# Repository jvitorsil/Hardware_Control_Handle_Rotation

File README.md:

# Hardware_Control_Handle_Rotation

Sistema embarcado para controle de rotação de punho em próteses bioelétricas através de sensores inerciais.

O sistema conta com a utilização de dois acelerometro acoplados ao paciente, acoplados respectivamente em paralelo na região antero-lateral do torax nos musculos intercostais e outro localizado no triceps braquial. O funcionamento está baseado na agulação criada entre os sensores pelo movimento de abdução do braço, gerando assim um movimento de pronação e supinação da protese.

O circuito eletronico conta com a utilização de um micrcontrolador STM32F103C8T6, com toda parte de Debug, reset e clock adicionada ao circuito. 

As proteses mioeletricas atuais contam na maioria das vezes com motores DC e para o acionamento do mesmo foi utilizado do driver L293D, que consegue controlar a velocidade e sentido de rotação do motor através da modulação dos pulsos de PWM gerado.

Já para a parte de entrada de dados foi definido o sensor MPU6050, contando com protocolo de comunicação I2C.

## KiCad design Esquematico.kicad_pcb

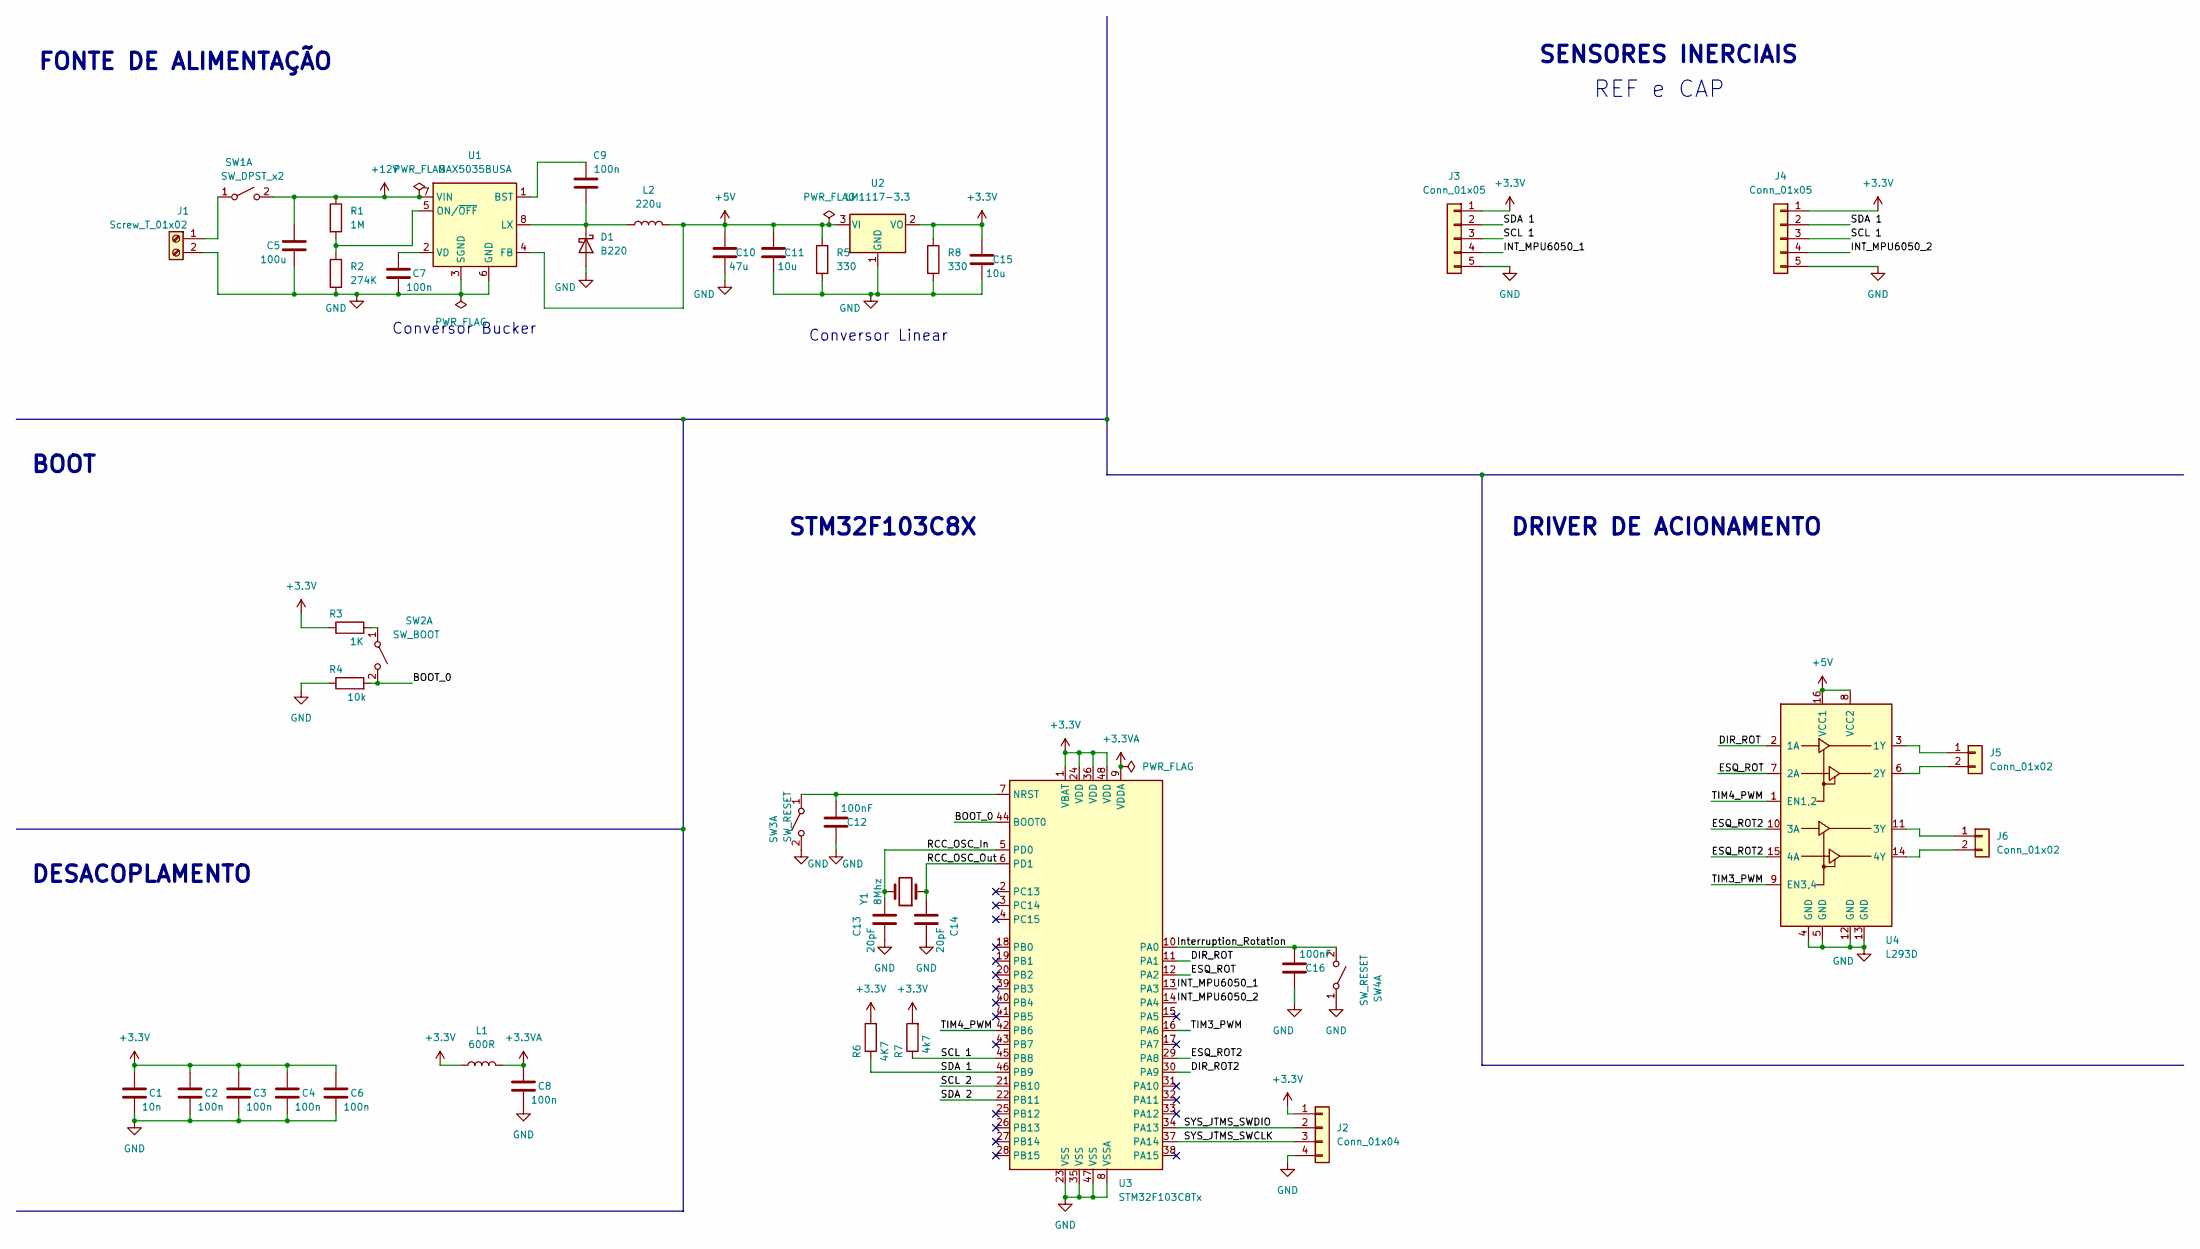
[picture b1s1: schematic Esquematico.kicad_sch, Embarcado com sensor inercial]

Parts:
C1: 10n; C_0402_1005Metric
C2, C3, C4, C6, C8: 100n; C_0402_1005Metric
C5: 100u; C_0805_2012Metric
C7, C9: 100n; C_0805_2012Metric
C10: 47u; C_0805_2012Metric
C11, C15: 10u; C_0805_2012Metric
C12, C16: 100nF; C_0402_1005Metric
C13, C14: 20pF; C_0603_1608Metric
D1: B220; D_SMF
J1: Screw_T_01x02; JST_PH_S2B-PH-SM4-TB_1x02-1MP_P2.00mm_Horizontal
J2: Conn_01x04; JST_PH_S4B-PH-SM4-TB_1x04-1MP_P2.00mm_Horizontal
J3, J4: Conn_01x05; JST_PH_S5B-PH-SM4-TB_1x05-1MP_P2.00mm_Horizontal
J5, J6: Conn_01x02; JST_PH_S2B-PH-SM4-TB_1x02-1MP_P2.00mm_Horizontal
L1: 600R; L_0603_1608Metric
L2: 220u; L_0603_1608Metric
R1: 1M; R_0805_2012Metric
R2: 274K; R_0805_2012Metric
R3: 1K; R_0805_2012Metric
R4: 10k; R_0805_2012Metric
R5, R8: 330; R_0805_2012Metric
R6: 4K7; R_0805_2012Metric
R7: 4k7; R_0805_2012Metric
SW1: SW_DPST_x2; SW_DIP_SPSTx01_Slide_6.7x4.1mm_W6.73mm_P2.54mm_LowProfile_J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
SW2: SW_BOOT; SW_SPST_B3U-1000P-B
SW3, SW4: SW_RESET; SW_SPST_B3U-1000P-B
U1: MAX5035BUSA; SOIC-8_3.9x4.9mm_P1.27mm
U2: LM1117-3.3; SOT-223-3_TabPin2
U3: STM32F103C8Tx; LQFP-48_7x7mm_P0.5mm
U4: L293D; DIP-16_W7.62mm
Y1: 8Mhz; Crystal_SMD_HC49-SD

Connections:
+3.3V: C1.1, C2.1, C3.1, C4.1, C6.1, C15.2, J2.1, J3.1, J4.1, L1.1, R3.1, R6.2, R7.2, R8.1, U2.2 (VO), U3.1 (VBAT), U3.24 (VDD), U3.36 (VDD), U3.48 (VDD)
+3.3VA: C8.1, L1.2, U3.9 (VDDA)
+5V: C10.2, C11.2, L2.2, R5.1, U1.4 (FB), U2.3 (VI), U4.8 (VCC2), U4.16 (VCC1)
+12V: C5.2, R1.1, SW1.2 (B), U1.7 (VIN)
/BOOT_0: R4.2, SW2.2 (B), U3.44 (BOOT0)
/DIR_ROT: U3.11 (PA1), U4.2 (1A)
/DIR_ROT2: U3.30 (PA9)
/ESQ_ROT: U3.12 (PA2), U4.7 (2A)
/ESQ_ROT2: U3.29 (PA8), U4.10 (3A), U4.15 (4A)
/INT_MPU6050_1: J3.4, U3.13 (PA3)
/INT_MPU6050_2: J4.4, U3.14 (PA4)
/Interruption_Rotation: C16.1, SW4.2 (B), U3.10 (PA0)
/RCC_OSC_In: C13.2, U3.5 (PD0), Y1.2
/RCC_OSC_Out: C14.2, U3.6 (PD1), Y1.1
/SCL 1: J3.3, J4.3, R7.1, U3.45 (PB8)
/SCL 2: U3.21 (PB10)
/SDA 1: J3.2, J4.2, R6.1, U3.46 (PB9)
/SDA 2: U3.22 (PB11)
/SYS_JTMS_SWCLK: J2.3, U3.37 (PA14)
/SYS_JTMS_SWDIO: J2.2, U3.34 (PA13)
/TIM3_PWM: U3.16 (PA6), U4.9 (EN3,4)
/TIM4_PWM: U3.42 (PB6), U4.1 (EN1,2)
GND: C1.2, C2.2, C3.2, C4.2, C5.1, C6.2, C7.1, C8.2, C10.1, C11.1, C12.2, C13.1, C14.1, C15.1, C16.2, D1.2 (A), J1.2, J2.4, J3.5, J4.5, R2.2, R4.1, R5.2, R8.2, SW3.2 (B), SW4.1 (A), U1.3 (SGND), U1.6 (GND), U2.1 (GND), U3.8 (VSSA), U3.23 (VSS), U3.35 (VSS), U3.47 (VSS), U4.4 (GND), U4.5 (GND), U4.12 (GND), U4.13 (GND)
unnamed: C7.2, U1.2 (VD)
unnamed: C9.1, D1.1 (K), L2.1, U1.8 (LX)
unnamed: C9.2, U1.1 (BST)
unnamed: C12.1, SW3.1 (A), U3.7 (NRST)
unnamed: J1.1, SW1.1 (A)
unnamed: J5.1, U4.3 (1Y)
unnamed: J5.2, U4.6 (2Y)
unnamed: J6.1, U4.11 (3Y)
unnamed: J6.2, U4.14 (4Y)
unnamed: R1.2, R2.1, U1.5 (ON/~OFF)
unnamed: R3.2, SW2.1 (A)

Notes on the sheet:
SENSORES INERCIAIS
REF e CAP
BOOT
DESACOPLAMENTO
STM32F103C8X
Conversor Bucker
FONTE DE ALIMENTAÇÃO
DRIVER DE ACIONAMENTO
Conversor Linear

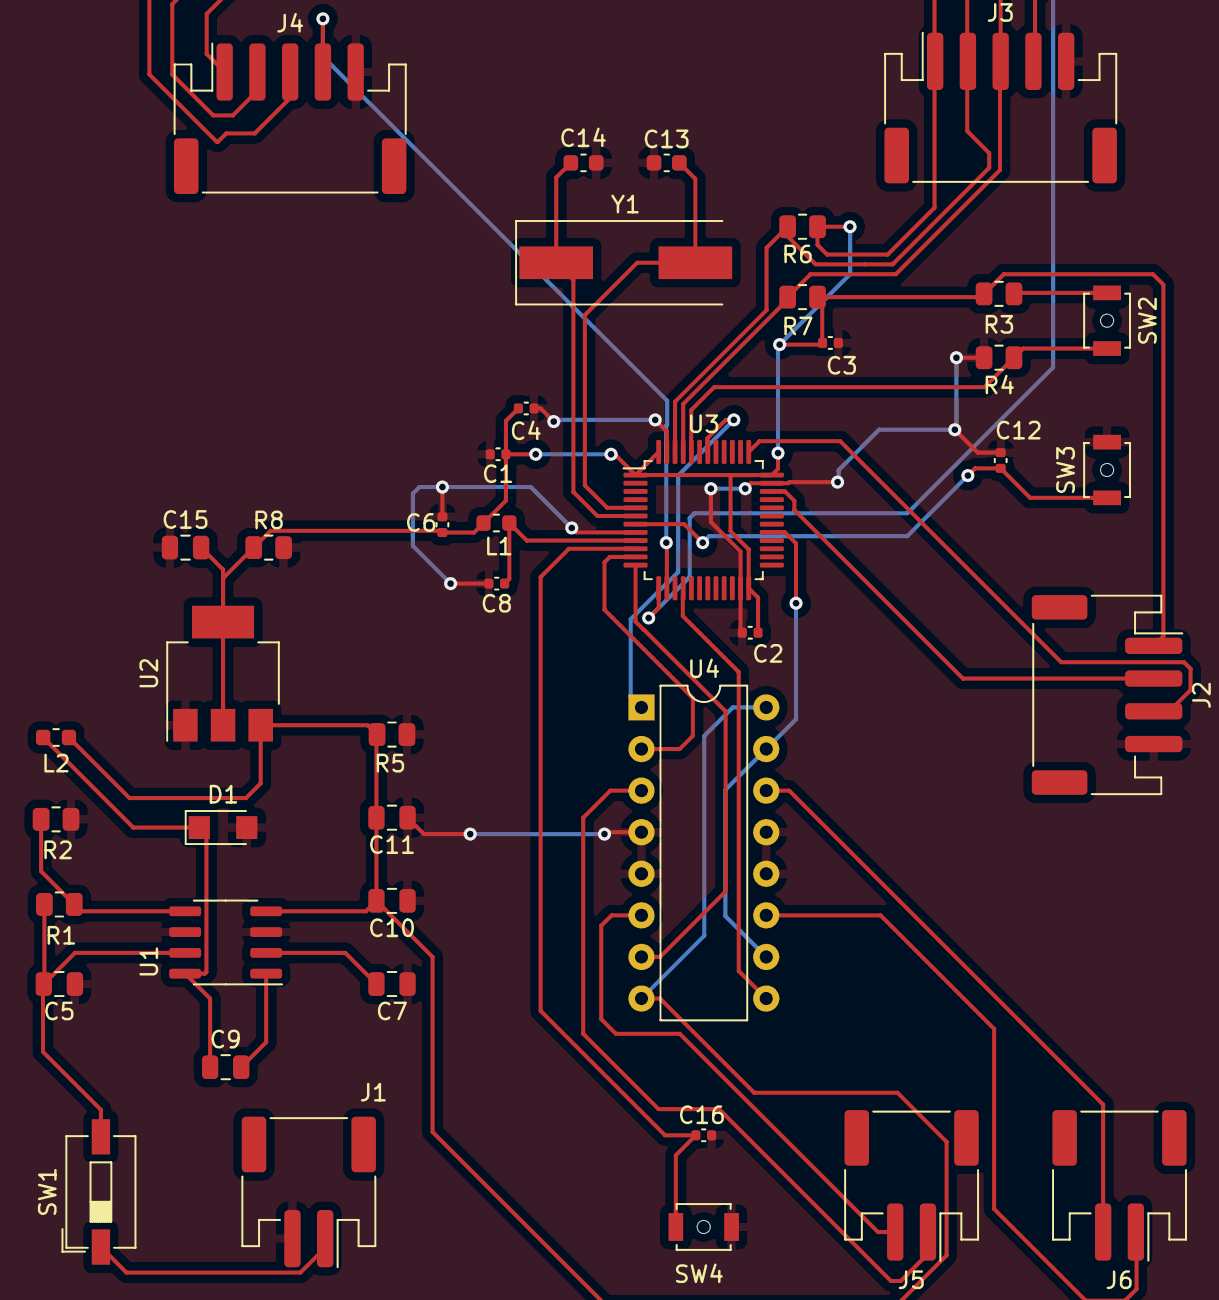
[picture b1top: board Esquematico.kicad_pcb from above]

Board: 2 copper layers, 42 parts (0 on the bottom side), 31 nets.

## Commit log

2023-06-29 feat: First Commmit
2023-06-29 docs(README.md): Update
